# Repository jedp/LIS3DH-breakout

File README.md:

# LIS3DH Breakout Board

Three-axis linear accelerometer. Configurable as I2C or SPI.

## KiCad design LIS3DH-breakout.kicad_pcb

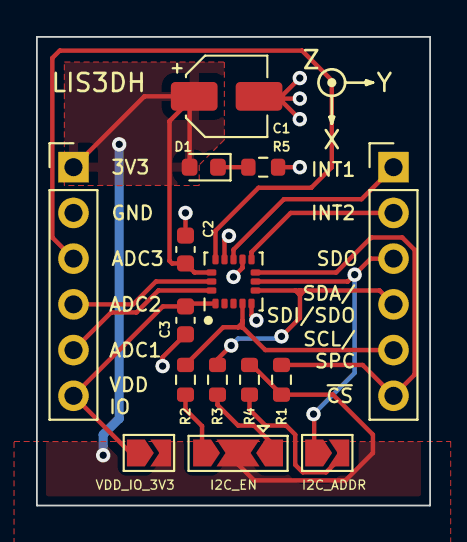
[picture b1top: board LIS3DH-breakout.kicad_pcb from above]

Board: 2 copper layers, 21.8 x 26.0 mm, 15 parts (0 on the bottom side), 16 nets.

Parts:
C1: 10µ; CP_Elec_4x4.5
C2, C3: 0.1µ; C_0603_1608Metric
D1: LED PWR; LED_0603_1608Metric
I2C_ADDR: I2C ADDR; SolderJumper-2_P1.3mm_Open_TrianglePad1.0x1.5mm
I2C_EN: I2C EN; SolderJumper-3_P2.0mm_Open_TrianglePad1.0x1.5mm
J1, J2: Conn_01x06_Female; PinHeader_1x06_P2.54mm_Vertical
LIS3DH: LIS3DH; LGA-16_3x3mm_P0.5mm_LayoutBorder3x5y
R1, R4: 100k; R_0603_1608Metric
R2, R3: 10k; R_0603_1608Metric
R5: 1k; R_0603_1608Metric
VDD_IO_3V3: VCC_IO = VCC; SolderJumper-2_P1.3mm_Open_TrianglePad1.0x1.5mm

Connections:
+3V3: C1.1, C2.1, D1.2 (A), I2C_EN.2 (C), J2.1, LIS3DH.14 (VDD), R1.1, R4.1, VDD_IO_3V3.2 (B)
ADC1: J2.5, LIS3DH.16 (ADC1)
ADC2: J2.4, LIS3DH.15 (ADC2)
ADC3: J2.3, LIS3DH.13 (ADC3)
CS/MODE: J1.6, LIS3DH.8 (CS), R1.2
GND: C1.2, C2.2, C3.2, J2.2, LIS3DH.5 (GND), LIS3DH.10 (GND), LIS3DH.12 (GND), R5.1
INT1: J1.1, LIS3DH.11 (INT1)
INT2: J1.2, LIS3DH.9 (INT2)
unnamed: D1.1 (K), R5.2
unnamed: I2C_EN.1 (A), R3.1
unnamed: I2C_EN.3 (B), R2.1
unnamed: I2C_ADDR.2 (B), R4.2
SCL/SPC: J1.5, LIS3DH.4 (SCL/SPC), R2.2
SDA/SDI/SDO: J1.4, LIS3DH.6 (SDA/SDI/SDO), R3.2
SDO/SA0: I2C_ADDR.1 (A), J1.3, LIS3DH.7 (SDO/SA0)
VDD_IO: C3.1, J2.6, LIS3DH.1 (VDD_IO), VDD_IO_3V3.1 (A)

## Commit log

2023-02-20 LIS3DH accelerometer breakout board
2023-02-20 added logo
